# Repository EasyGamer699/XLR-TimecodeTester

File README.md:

# XLR-TimecodeTester

### 🚧 This is Work in Progress.... 🚧

A compact device for testing and verifying timecode signals transmitted over XLR. It detects and analyzes LTC signals to ensure stable synchronization, making it ideal for live, studio, and broadcast environments.

## ⚙️ Features

- ✅ Tests and verifies LTC timecode over XLR
- ✅ Detects presence and signal stability
- ✅ Displays current timecode (HH:MM:SS:FF)
- ✅ Portable and compact design
- ✅ Helps diagnose sync and signal issues
- ✅ Plug-and-play operation

## 🔥 Acknowledgements

- [Kicad JLC PCB BOM generator](https://github.com/Bouni/kicad-jlcpcb-tools)
- [Kicad JLC PCB Parts Libary ](https://github.com/CDFER/JLCPCB-Kicad-Library)

## License

This project is licensed under the terms of the **Creative Commons Attribution-NonCommercial 4.0 International License**.

You are free to share and adapt the material, provided that you give appropriate credit and do not use the material for commercial purposes.

The full legal text of the license can be found in the [LICENSE](LICENSE.md) file or at [creativecommons.org](https://creativecommons.org/licenses/by-nc/4.0/legalcode).

---

Copyright (c) 2026 Aaron Stodt

For commercial licensing inquiries or further questions, please contact me at: [stodtaaron@gmail.com](mailto:stodtaaron@gmail.com)

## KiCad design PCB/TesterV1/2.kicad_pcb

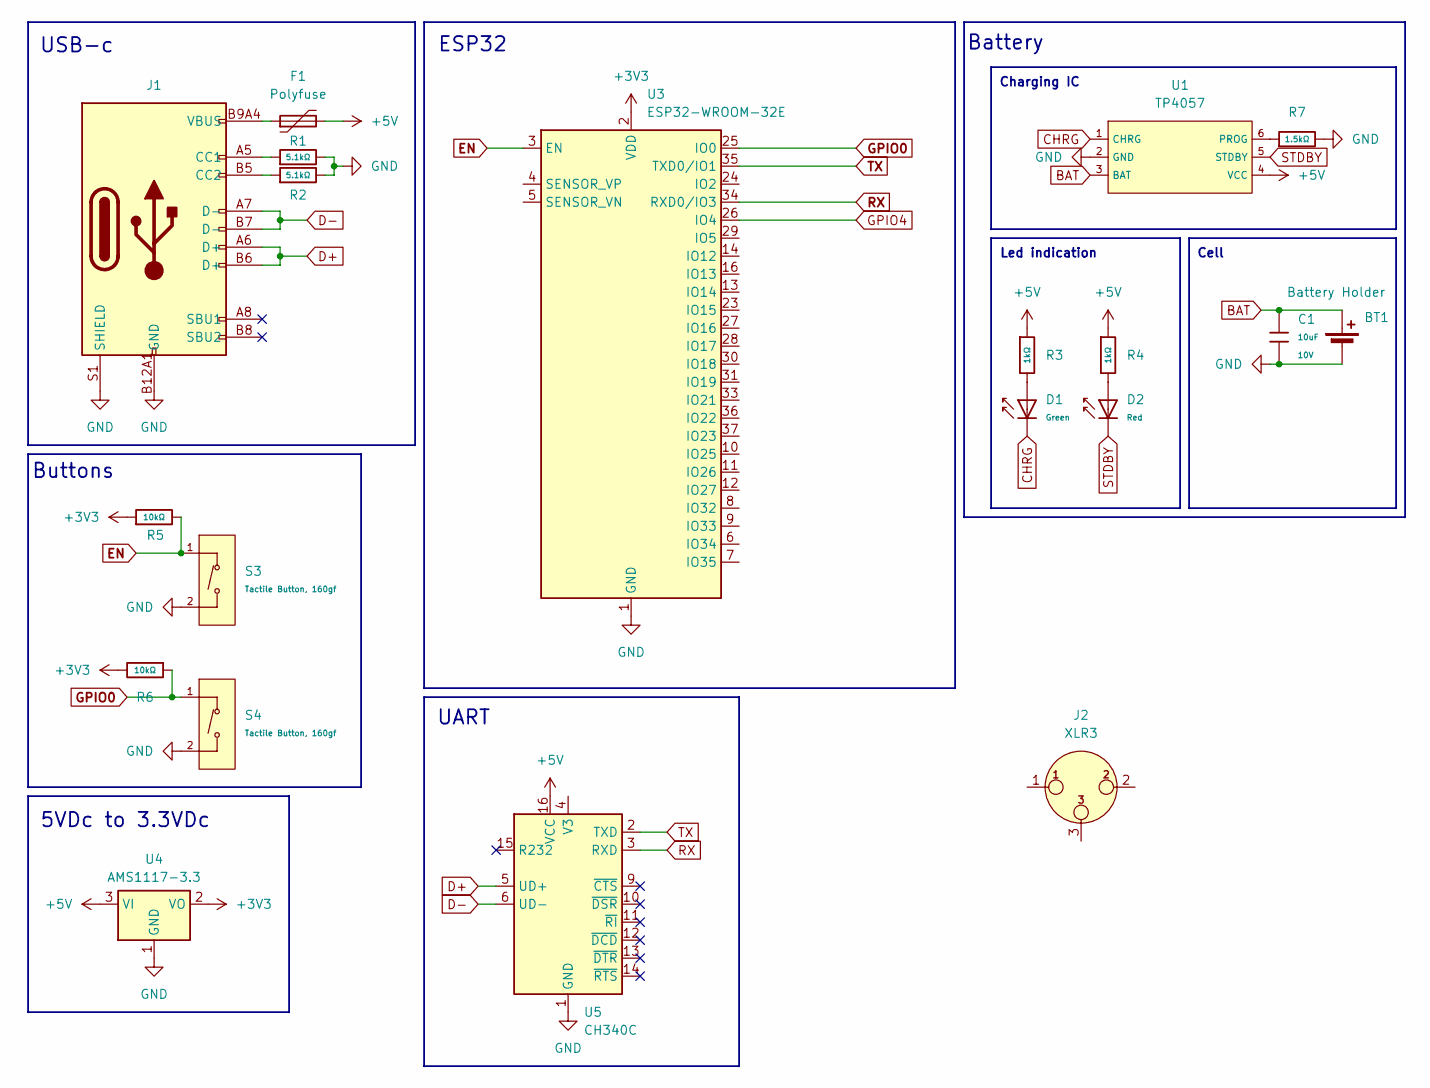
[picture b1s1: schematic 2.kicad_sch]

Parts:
BT1: Battery Holder; BatteryHolder_MPD_BH-18650-PC2
C1: 10uF; C_0603; Voltage Rated 10V; Tolerance ±10%; Part CL10A106KP8NNNC; LCSC C19702
D1: Green; D_0805; Part KT-0805G; LCSC C2297
D2: Red; D_0805; Forward Voltage (VF) 1.6V~2.6V; Part NCD0805R1; LCSC C84256
F1: Polyfuse; Fuse_0805_2012Metric
J1: Connector, USB-TYPE-C-16P; TYPE-C-SMD_HX-TYPE-C-16PIN; LCSC C2927039
J2: XLR3; Jack_XLR_Neutrik_NC3FAAH-0_Horizontal
R1, R2: 5.1kΩ; R_0402; Overload Voltage (Max) 50V; Tolerance ±1%; Part 0402WGF5101TCE; LCSC C25905
R3, R4: 1kΩ; R_0402; Overload Voltage (Max) 50V; Tolerance ±1%; Part 0402WGF1001TCE; LCSC C11702
R5, R6: 10kΩ; R_0805; Overload Voltage (Max) 150V; Tolerance ±1%; Part 0805W8F1002T5E; LCSC C17414
R7: 1.5kΩ; R_0402; Overload Voltage (Max) 50V; Tolerance ±1%; Part 0402WGF1501TCE; LCSC C25867
S3, S4: Tactile Button, 160gf; SW_TS-1088-AR02016; Voltage Rating (Dc) 12V; Part TS-1088-AR02016; LCSC C720477
U1: TP4057; SOT-23-6_L2.9-W1.6-P0.95-LS2.8-BL; Part TP4057-42-SOT26-R; LCSC C12044
U3: ESP32-WROOM-32E; ESP32-WROOM-32D
U4: AMS1117-3.3; SOT-223-3_TabPin2
U5: CH340C; SOIC-16_3.9x9.9mm_P1.27mm

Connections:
+3V3: R5.1, R6.2, U3.2 (VDD), U4.2 (VO)
+5V: F1.2, R3.1, R4.1, U1.4 (VCC), U4.3 (VI), U5.16 (VCC)
BAT: BT1.1 (+), C1.1, U1.3 (BAT)
CHRG: D1.1, U1.1 (CHRG)
D+: J1.A6 (D+), J1.B6 (D+), U5.5 (UD+)
D-: J1.A7 (D-), J1.B7 (D-), U5.6 (UD-)
EN: R5.2, S3.1 (A), U3.3 (EN)
GND: BT1.2 (-), C1.2, J1.A12B1 (GND), J1.B12A1 (GND), J1.S1 (SHIELD), R1.2, R2.2, R7.2, S3.2 (B), S4.2 (B), U1.2 (GND), U3.1 (GND), U3.15 (GND), U3.38 (GND), U3.39 (GND), U4.1 (GND), U5.1 (GND)
GPIO0: R6.1, S4.1 (A), U3.25 (IO0)
GPIO4: U3.26 (IO4)
unnamed: D1.2, R3.2
unnamed: D2.2, R4.2
unnamed: F1.1, J1.A9B4 (VBUS), J1.B9A4 (VBUS)
unnamed: J1.A5 (CC1), R1.1
unnamed: J1.B5 (CC2), R2.1
unnamed: R7.1, U1.6 (PROG)
RX: U3.34 (RXD0/IO3), U5.3 (RXD)
STDBY: D2.1, U1.5 (STDBY)
TX: U3.35 (TXD0/IO1), U5.2 (TXD)

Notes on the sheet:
Led indication
Cell
UART
USB-c
Charging IC
5VDc to 3.3VDc
Battery
ESP32
Buttons

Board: 4 copper layers, 20 parts (2 on the bottom side), 18 nets, no tracks yet.

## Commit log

2026-02-26 Mark README as work in progress
    Update README to indicate the project is a work in progress by adding 'Work in progress ...' and adjusting whitespace/formatting in the file.
2026-03-04 Add PCB/TesterV1 KiCad project and backups
    Add the complete TesterV1 KiCad project and related artifacts. Includes .kicad_pcb, .kicad_prl, .kicad_pro, .kicad_sch, fabrication-toolkit-options.json, fp-info-cache, JLCPCB project DB, multiple ti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
2026-03-04 Add CC BY-NC 4.0 license and update README
    Add full Creative Commons Attribution-NonCommercial 4.0 International license as LICENSE.md and expand README.md from a placeholder to a detailed project overview. README now includes a work-in-progr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
2026-03-04 Update README.md
    Readme update
2026-03-11 Update PCB footprints, nets and ignore PCB/
    Add .gitignore to exclude PCB/ and apply multiple PCB library updates: rename nets (e.g. VCC->BAT, CHRG, STDBY), reassign nets on several pads, and update schematic and fp-info-cache. Replace/update 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
2026-03-11 Add PCB Tester backups and interactive BOM
    Remove .gitignore entry for PCB/ and add PCB project artifacts: multiple backup ZIPs under PCB/TesterV1/2-backups (2026-03-07 and 2026-03-11) and an interactive BOM HTML at PCB/TesterV1/bom/ibom.html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
